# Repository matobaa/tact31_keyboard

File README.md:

# tact31_keyboard
A 30% keyboard with tactile switches

- [Build Guide](doc/build.md)

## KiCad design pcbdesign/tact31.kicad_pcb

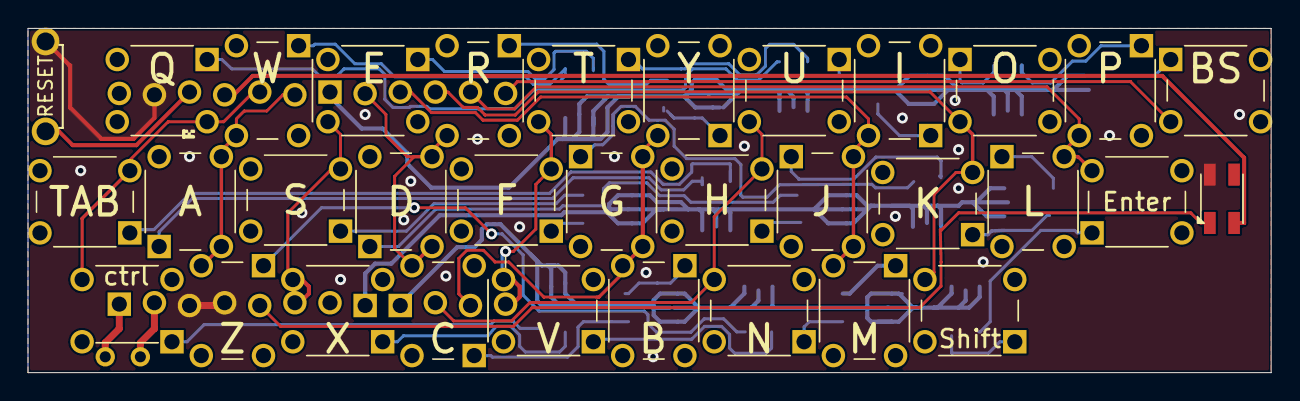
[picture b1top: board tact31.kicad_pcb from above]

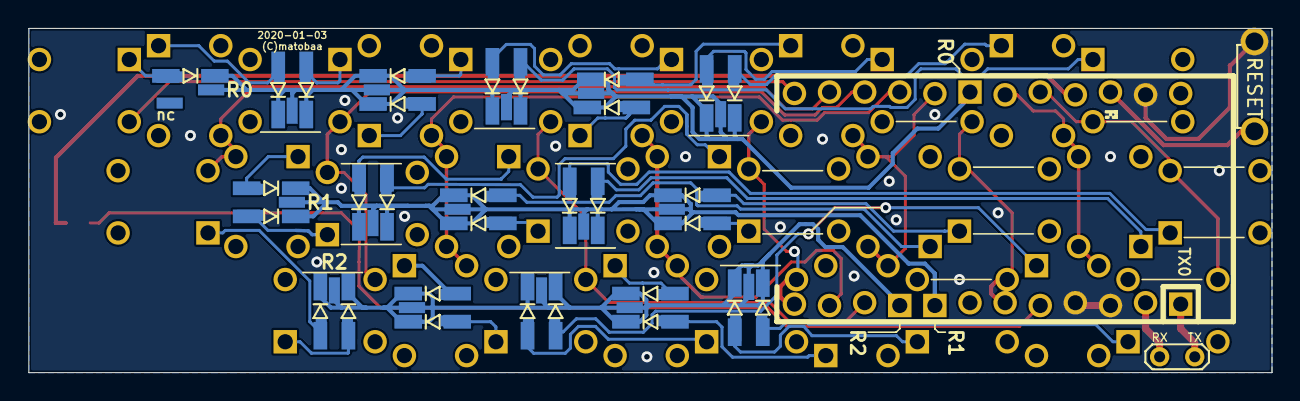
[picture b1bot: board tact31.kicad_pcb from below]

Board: 2 copper layers, 89.9 x 24.9 mm, 82 parts (47 on the bottom side), 51 nets.

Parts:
D_A1: D; D3_SMD_v2
D_B1: D; D3_SMD_v2
D_C1: D; D3_SMD_v2
D_CB1: D_x2_KCom_AAK; SOT-23_Handsoldering
D_CTRL1: D; D3_SMD_v2
D_D1: D; D3_SMD_v2
D_DEL1: D; D3_SMD_v2
D_DELX1: D_x2_KCom_AAK; SOT-23_Handsoldering
D_E1: D; D3_SMD_v2
D_ENTER1: D; D3_SMD_v2
D_ENTSFT1: D_x2_KCom_AAK; SOT-23_Handsoldering
D_F1: D; D3_SMD_v2
D_G1: D; D3_SMD_v2
D_GJ1: D_x2_KCom_AAK; SOT-23_Handsoldering
D_H1: D; D3_SMD_v2
D_HD1: D_x2_KCom_AAK; SOT-23_Handsoldering
D_I1: D; D3_SMD_v2
D_IU1: D_x2_KCom_AAK; SOT-23_Handsoldering
D_J1: D; D3_SMD_v2
D_K1: D; D3_SMD_v2
D_L1: D; D3_SMD_v2
D_LK1: D_x2_KCom_AAK; SOT-23_Handsoldering
D_M1: D; D3_SMD_v2
D_N1: D; D3_SMD_v2
D_NM1: D_x2_KCom_AAK; SOT-23_Handsoldering
D_O1: D; D3_SMD_v2
D_OP1: D_x2_KCom_AAK; SOT-23_Handsoldering
D_P1: D; D3_SMD_v2
D_Q1: D; D3_SMD_v2
D_R1: D; D3_SMD_v2
D_S1: D; D3_SMD_v2
D_SD1: D_x2_KCom_AAK; SOT-23_Handsoldering
D_SHIFT1: D; D3_SMD_v2
D_T1: D; D3_SMD_v2
D_TA1: D_x2_KCom_AAK; SOT-23_Handsoldering
D_TAB1: D; D3_SMD_v2
D_TW1: D_x2_KCom_AAK; SOT-23_Handsoldering
D_U1: D; D3_SMD_v2
D_V1: D; D3_SMD_v2
D_W1: D; D3_SMD_v2
D_WE1: D_x2_KCom_AAK; SOT-23_Handsoldering
D_X1: D; D3_SMD_v2
D_XCTL1: D_x2_KCom_AAK; SOT-23_Handsoldering
D_Y1: D; D3_SMD_v2
D_YR1: D_x2_KCom_AAK; SOT-23_Handsoldering
D_Z1: D; D3_SMD_v2
D_ZV1: D_x2_KCom_AAK; SOT-23_Handsoldering
LED1: SK6812MINI; LED_SK6812MINI_PLCC4_3.5x3.5mm_P1.75mm
SW1: SW_PUSH; ResetSW
SW_A1: SW_Push; SW_PUSH_6mm_H8mm
SW_B1: SW_Push; SW_PUSH_6mm_H8mm
SW_C1: SW_Push; SW_PUSH_6mm_H8mm
SW_CTRL1: SW_Push; SW_PUSH_6mm_H8mm
SW_D1: SW_Push; SW_PUSH_6mm_H8mm
SW_DEL1: SW_Push; SW_PUSH_6mm_H8mm
SW_E1: SW_Push; SW_PUSH_6mm_H8mm
SW_ENTER1: SW_Push; SW_PUSH_6mm_H8mm
SW_F1: SW_Push; SW_PUSH_6mm_H8mm
SW_G1: SW_Push; SW_PUSH_6mm_H8mm
SW_H1: SW_Push; SW_PUSH_6mm_H8mm
SW_I1: SW_Push; SW_PUSH_6mm_H8mm
SW_J1: SW_Push; SW_PUSH_6mm_H8mm
SW_K1: SW_Push; SW_PUSH_6mm_H8mm
SW_L1: SW_Push; SW_PUSH_6mm_H8mm
SW_M1: SW_Push; SW_PUSH_6mm_H8mm
SW_N1: SW_Push; SW_PUSH_6mm_H8mm
SW_O1: SW_Push; SW_PUSH_6mm_H8mm
SW_P1: SW_Push; SW_PUSH_6mm_H8mm
SW_Q1: SW_Push; SW_PUSH_6mm_H8mm
SW_R1: SW_Push; SW_PUSH_6mm_H8mm
SW_S1: SW_Push; SW_PUSH_6mm_H8mm
SW_SHIFT1: SW_Push; SW_PUSH_6mm_H8mm
SW_T1: SW_Push; SW_PUSH_6mm_H8mm
SW_TAB1: SW_Push; SW_PUSH_6mm_H8mm
SW_U1: SW_Push; SW_PUSH_6mm_H8mm
SW_V1: SW_Push; SW_PUSH_6mm_H8mm
SW_W1: SW_Push; SW_PUSH_6mm_H8mm
SW_X1: SW_Push; SW_PUSH_6mm_H8mm
SW_Y1: SW_Push; SW_PUSH_6mm_H8mm
SW_Z1: SW_Push; SW_PUSH_6mm_H8mm
TP1: TestPoint_2Pole; TestPoint_2Pads_Pitch2.54mm_Drill0.8mm
U1: ProMicro; ArduinoProMicro

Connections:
/C0: SW_CTRL1.1, SW_Q1.1, SW_TAB1.1, U1.20
/C1: SW_A1.1, SW_W1.1, SW_Z1.1, U1.19
/C2: SW_E1.1, SW_S1.1, SW_X1.1, U1.6
/C3: SW_C1.1, SW_D1.1, SW_R1.1, U1.17
/C4: SW_F1.1, SW_T1.1, SW_V1.1, U1.12
/C5: SW_B1.1, SW_G1.1, SW_Y1.1, U1.11
/C6: SW_H1.1, SW_N1.1, SW_U1.1, U1.10
/C7: SW_I1.1, SW_J1.1, SW_M1.1, U1.16
/C8: SW_K1.1, SW_O1.1, SW_SHIFT1.1, U1.15
/C9: SW_ENTER1.1, SW_L1.1, SW_P1.1, U1.14
/CA: SW_DEL1.1, U1.13
/LED: LED1.3, U1.5
/R0: D_DEL1.1, D_DELX1.3, D_E1.1, D_I1.1, D_IU1.3, D_O1.1, D_OP1.3, D_P1.1, D_Q1.1, D_R1.1, D_T1.1, D_TW1.3, D_U1.1, D_W1.1, D_WE1.3, D_Y1.1, D_YR1.3, U1.18
/R1: D_A1.1, D_D1.1, D_F1.1, D_G1.1, D_GJ1.3, D_H1.1, D_HD1.3, D_J1.1, D_K1.1, D_L1.1, D_LK1.3, D_S1.1, D_SD1.3, D_TA1.3, D_TAB1.1, U1.8
/R2: D_B1.1, D_C1.1, D_CB1.3, D_CTRL1.1, D_ENTER1.1, D_ENTSFT1.3, D_M1.1, D_N1.1, D_NM1.3, D_SHIFT1.1, D_V1.1, D_X1.1, D_XCTL1.3, D_Z1.1, D_ZV1.3, U1.9
/RST: SW1.1, U1.22
/RX: TP1.2, U1.2
/TX: TP1.1, U1.1
GND: LED1.2, SW1.2, U1.3, U1.4, U1.23
unnamed: D_A1.2, D_TA1.1, SW_A1.2
unnamed: D_B1.2, D_CB1.2, SW_B1.2
unnamed: D_C1.2, D_CB1.1, SW_C1.2
unnamed: D_CTRL1.2, D_XCTL1.2, SW_CTRL1.2
unnamed: D_D1.2, D_HD1.2, SW_D1.2
unnamed: D_DEL1.2, D_DELX1.1, SW_DEL1.2
unnamed: D_E1.2, D_WE1.2, SW_E1.2
unnamed: D_ENTER1.2, D_ENTSFT1.1, SW_ENTER1.2
unnamed: D_ENTSFT1.2, D_SHIFT1.2, SW_SHIFT1.2
unnamed: D_F1.2, D_SD1.1, SW_F1.2
unnamed: D_G1.2, D_GJ1.1, SW_G1.2
unnamed: D_GJ1.2, D_J1.2, SW_J1.2
unnamed: D_H1.2, D_HD1.1, SW_H1.2
unnamed: D_I1.2, D_IU1.1, SW_I1.2
unnamed: D_IU1.2, D_U1.2, SW_U1.2
unnamed: D_K1.2, D_LK1.2, SW_K1.2
unnamed: D_L1.2, D_LK1.1, SW_L1.2
unnamed: D_M1.2, D_NM1.2, SW_M1.2
unnamed: D_N1.2, D_NM1.1, SW_N1.2
unnamed: D_O1.2, D_OP1.1, SW_O1.2
unnamed: D_OP1.2, D_P1.2, SW_P1.2
unnamed: D_Q1.2, D_TW1.1, SW_Q1.2
unnamed: D_R1.2, D_YR1.2, SW_R1.2
unnamed: D_S1.2, D_SD1.2, SW_S1.2
unnamed: D_T1.2, D_TW1.2, SW_T1.2
unnamed: D_TA1.2, D_TAB1.2, SW_TAB1.2
unnamed: D_V1.2, D_ZV1.1, SW_V1.2
unnamed: D_W1.2, D_WE1.1, SW_W1.2
unnamed: D_X1.2, D_XCTL1.1, SW_X1.2
unnamed: D_Y1.2, D_YR1.1, SW_Y1.2
unnamed: D_Z1.2, D_ZV1.2, SW_Z1.2
VCC: LED1.4, U1.21

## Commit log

2020-04-05 Add a firmware
2020-04-05 move all into firmware
2020-04-19 build guide
2020-04-19 fix a missing image
2020-04-20 add pcb design
